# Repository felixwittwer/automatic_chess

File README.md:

# automatic_chess

## grbl firmware v1.1 for movement

[https://github.com/gnea/grbl](https://github.com/gnea/grbl)

Follow the original guide for installation and compilation: [https://github.com/gnea/grbl/wiki/Compiling-Grbl](https://github.com/gnea/grbl/wiki/Compiling-Grbl)

Instead of the original Repository the cusomt configuration in this repository should be used.

##

[Diagram in PDF form](./circuit_diagrams/Diagram.pdf)

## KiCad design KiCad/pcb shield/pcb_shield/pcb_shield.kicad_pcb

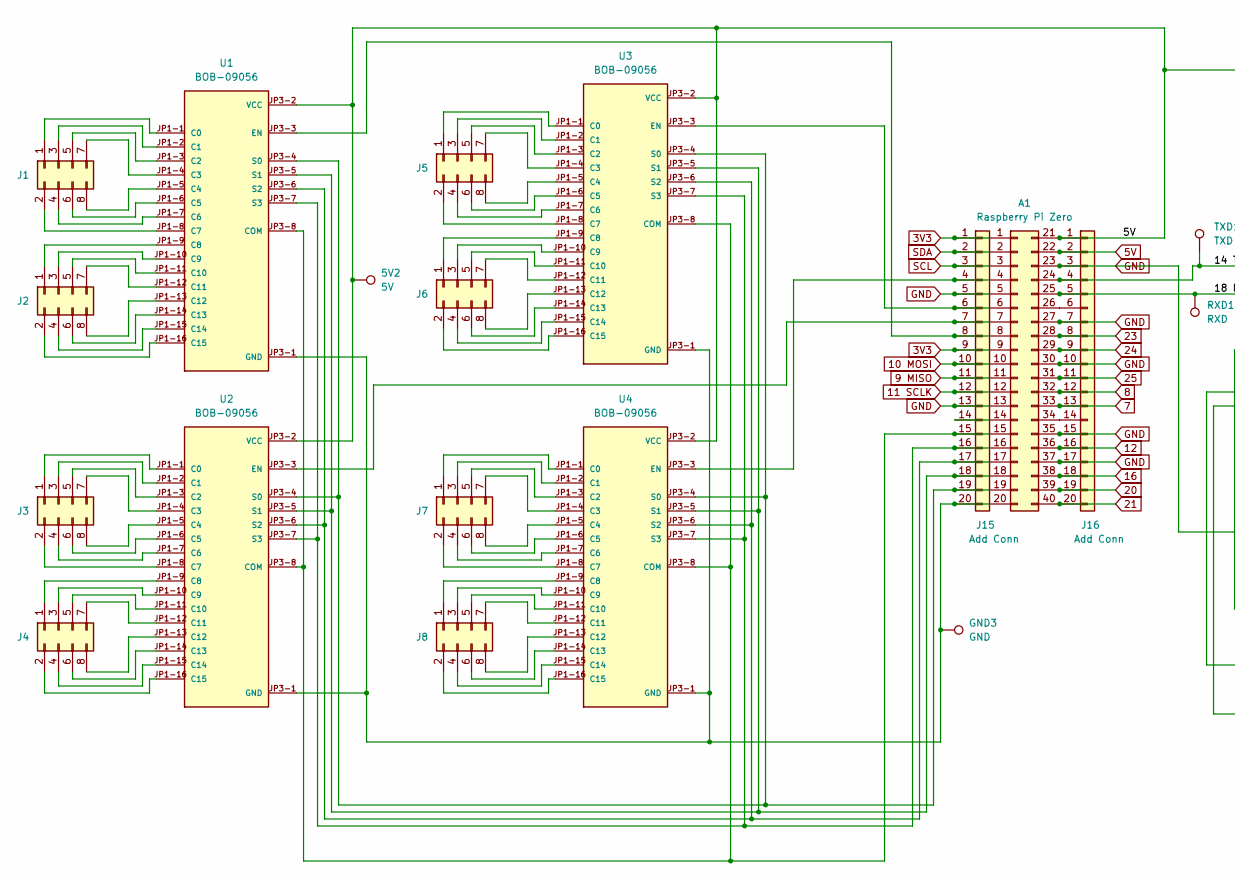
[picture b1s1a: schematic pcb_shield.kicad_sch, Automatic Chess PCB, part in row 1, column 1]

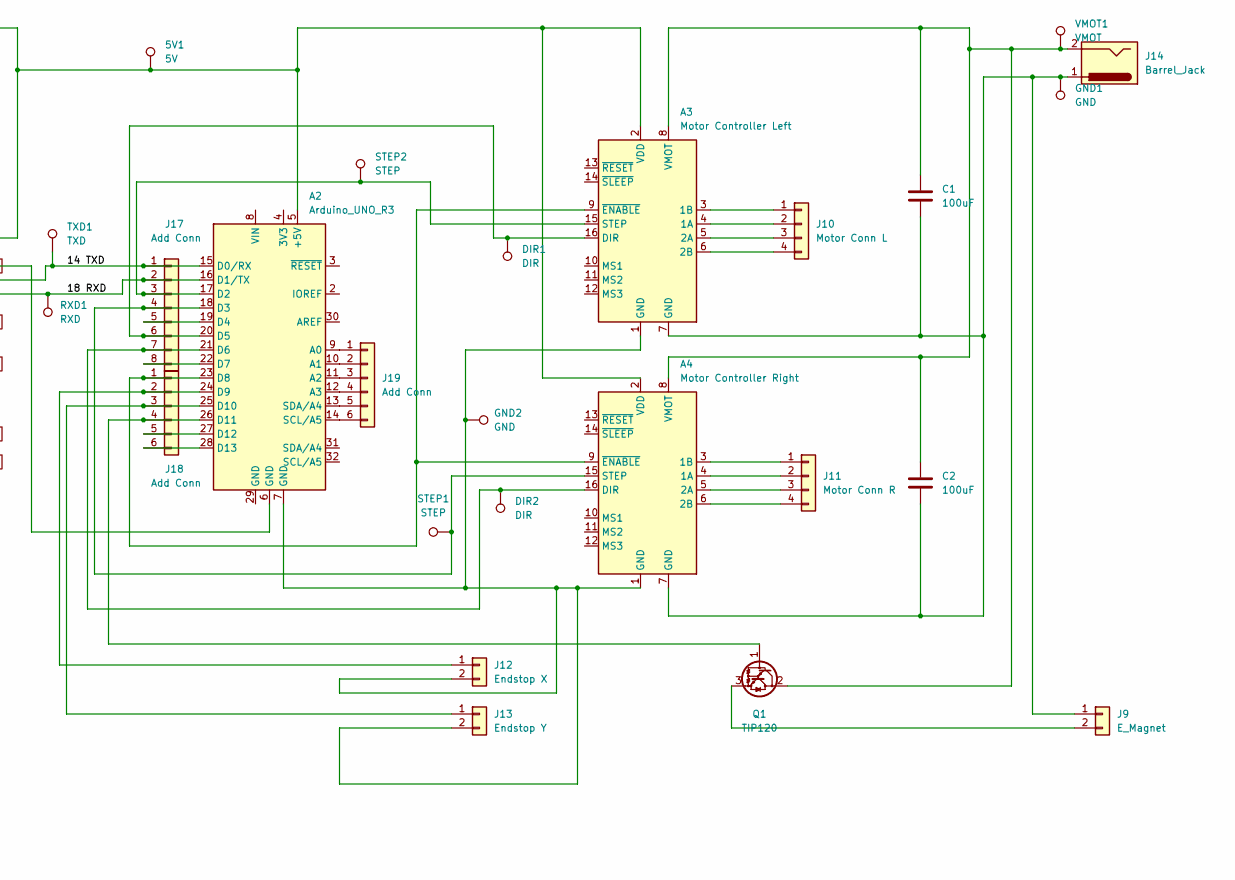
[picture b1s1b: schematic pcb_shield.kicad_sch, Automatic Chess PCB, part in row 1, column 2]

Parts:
5V1, 5V2: 5V; TestPoint_Pad_D2.0mm
A1: Raspberry Pi Zero; PinSocket_2x20_P2.54mm_Vertical
A2: Arduino_UNO_R3
A3: Motor Controller Left; Pololu_Breakout-16_15.2x20.3mm
A4: Motor Controller Right; Pololu_Breakout-16_15.2x20.3mm
C1, C2: 100uF; CP_Radial_D5.0mm_P2.50mm
DIR1, DIR2: DIR; TestPoint_Pad_D2.0mm
GND1, GND2, GND3: GND; TestPoint_Pad_D2.0mm
J1, J2, J3, J4, J5, J6, J7, J8: PinHeader_2x04_P2.54mm_Vertical
J9: E_Magnet; PinHeader_1x02_P2.54mm_Vertical
J10: Motor Conn L; PinHeader_1x04_P2.54mm_Vertical
J11: Motor Conn R; PinHeader_1x04_P2.54mm_Vertical
J12: Endstop X; PinHeader_1x02_P2.54mm_Vertical
J13: Endstop Y; PinHeader_1x02_P2.54mm_Vertical
J14: Barrel_Jack; TerminalBlock_Phoenix_MKDS-1,5-2_1x02_P5.00mm_Horizontal
J15, J16: Add Conn; PinSocket_1x20_P2.54mm_Vertical
J17: Add Conn; PinHeader_1x08_P2.54mm_Vertical
J18, J19: Add Conn; PinHeader_1x06_P2.54mm_Vertical
Q1: TIP120; TO-220-3_Vertical
RXD1: RXD; TestPoint_Pad_D2.0mm
STEP1, STEP2: STEP; TestPoint_Pad_D2.0mm
TXD1: TXD; TestPoint_Pad_D2.0mm
U1, U2, U3, U4: BOB-09056; MODULE_BOB-09056; PARTREV v11
VMOT1: VMOT; TestPoint_Pad_D2.0mm

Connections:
3V3: A1.1, A1.9, J15.1, J15.9
5V: 5V1.1, 5V2.1, A1.21, A1.22, A2.5 (+5V), A3.2 (VDD), A4.2 (VDD), J16.1, J16.2, U1.JP3-2 (VCC), U2.JP3-2 (VCC), U3.JP3-2 (VCC), U4.JP3-2 (VCC)
7: A1.33, J16.13
8: A1.32, J16.12
9 MISO: A1.11, J15.11
10 MOSI: A1.10, J15.10
11 SCLK: A1.12, J15.12
12: A1.36, J16.16
16: A1.38, J16.18
20: A1.39, J16.19
21: A1.40, J16.20
23: A1.28, J16.8
24: A1.29, J16.9
25: A1.31, J16.11
/14 TXD: A1.24, A2.15 (D0/RX), J16.4, J17.1, TXD1.1
/18 RXD: A1.25, A2.16 (D1/TX), J16.5, J17.2, RXD1.1
GND: A1.5, A1.13, A1.23, A1.27, A1.30, A1.35, A1.37, A2.6 (GND), J15.5, J15.13, J16.3, J16.7, J16.10, J16.15, J16.17
unnamed: A1.4, J15.4, U4.JP3-3 (EN)
unnamed: A1.6, J15.6, U3.JP3-3 (EN)
unnamed: A1.7, J15.7, U2.JP3-3 (EN)
unnamed: A1.8, J15.8, U1.JP3-3 (EN)
unnamed: A1.14, J15.14
unnamed: A1.15, J15.15, U1.JP3-8 (COM), U2.JP3-8 (COM), U3.JP3-8 (COM), U4.JP3-8 (COM)
unnamed: A1.16, J15.16, U1.JP3-7 (S3), U2.JP3-7 (S3), U3.JP3-7 (S3), U4.JP3-7 (S3)
unnamed: A1.17, J15.17, U1.JP3-6 (S2), U2.JP3-6 (S2), U3.JP3-6 (S2), U4.JP3-6 (S2)
unnamed: A1.18, J15.18, U1.JP3-5 (S1), U2.JP3-5 (S1), U3.JP3-5 (S1), U4.JP3-5 (S1)
unnamed: A1.19, J15.19, U1.JP3-4 (S0), U2.JP3-4 (S0), U3.JP3-4 (S0), U4.JP3-4 (S0)
unnamed: A1.20, GND3.1, J15.20, U1.JP3-1 (GND), U2.JP3-1 (GND), U3.JP3-1 (GND), U4.JP3-1 (GND)
unnamed: A1.26, J16.6
unnamed: A1.34, J16.14
unnamed: A2.7 (GND), A3.1 (GND), A4.1 (GND), GND2.1, J12.2, J13.2
unnamed: A2.9 (A0), J19.1
unnamed: A2.10 (A1), J19.2
unnamed: A2.11 (A2), J19.3
unnamed: A2.12 (A3), J19.4
unnamed: A2.13 (SDA/A4), J19.5
unnamed: A2.14 (SCL/A5), J19.6
unnamed: A2.17 (D2), A3.15 (STEP), J17.3, STEP2.1
unnamed: A2.18 (D3), A4.15 (STEP), J17.4, STEP1.1
unnamed: A2.19 (D4), J17.5
unnamed: A2.20 (D5), A3.16 (DIR), DIR1.1, J17.6
unnamed: A2.21 (D6), A4.16 (DIR), DIR2.1, J17.7
unnamed: A2.22 (D7), J17.8
unnamed: A2.23 (D8), A3.9 (~ENABLE), A4.9 (~ENABLE), J18.1
unnamed: A2.24 (D9), J12.1, J18.2
unnamed: A2.25 (D10), J13.1, J18.3
unnamed: A2.26 (D11), J18.4, Q1.1 (B)
unnamed: A2.27 (D12), J18.5
unnamed: A2.28 (D13), J18.6
unnamed: A3.3 (1B), J10.1
unnamed: A3.4 (1A), J10.2
unnamed: A3.5 (2A), J10.3
unnamed: A3.6 (2B), J10.4
unnamed: A3.7 (GND), A4.7 (GND), C1.2, C2.2, GND1.1, J9.1, J14.1
unnamed: A3.8 (VMOT), A4.8 (VMOT), C1.1, C2.1, J14.2, Q1.2 (C), VMOT1.1
unnamed: A4.3 (1B), J11.1
unnamed: A4.4 (1A), J11.2
unnamed: A4.5 (2A), J11.3
unnamed: A4.6 (2B), J11.4
unnamed: J1.1, U1.JP1-1 (C0)
unnamed: J1.2, U1.JP1-8 (C7)
unnamed: J1.3, U1.JP1-2 (C1)
unnamed: J1.4, U1.JP1-7 (C6)
unnamed: J1.5, U1.JP1-3 (C2)
unnamed: J1.6, U1.JP1-6 (C5)
unnamed: J1.7, U1.JP1-4 (C3)
unnamed: J1.8, U1.JP1-5 (C4)
unnamed: J2.1, U1.JP1-9 (C8)
unnamed: J2.2, U1.JP1-16 (C15)
unnamed: J2.3, U1.JP1-10 (C9)
unnamed: J2.4, U1.JP1-15 (C14)
unnamed: J2.5, U1.JP1-11 (C10)
unnamed: J2.6, U1.JP1-14 (C13)
unnamed: J2.7, U1.JP1-12 (C11)
unnamed: J2.8, U1.JP1-13 (C12)
unnamed: J3.1, U2.JP1-1 (C0)
unnamed: J3.2, U2.JP1-8 (C7)
unnamed: J3.3, U2.JP1-2 (C1)
unnamed: J3.4, U2.JP1-7 (C6)
unnamed: J3.5, U2.JP1-3 (C2)
unnamed: J3.6, U2.JP1-6 (C5)
unnamed: J3.7, U2.JP1-4 (C3)
unnamed: J3.8, U2.JP1-5 (C4)
unnamed: J4.1, U2.JP1-9 (C8)
unnamed: J4.2, U2.JP1-16 (C15)
unnamed: J4.3, U2.JP1-10 (C9)
unnamed: J4.4, U2.JP1-15 (C14)
unnamed: J4.5, U2.JP1-11 (C10)
unnamed: J4.6, U2.JP1-14 (C13)
unnamed: J4.7, U2.JP1-12 (C11)
unnamed: J4.8, U2.JP1-13 (C12)
unnamed: J5.1, U3.JP1-1 (C0)
unnamed: J5.2, U3.JP1-8 (C7)
unnamed: J5.3, U3.JP1-2 (C1)
unnamed: J5.4, U3.JP1-7 (C6)
unnamed: J5.5, U3.JP1-3 (C2)
unnamed: J5.6, U3.JP1-6 (C5)
unnamed: J5.7, U3.JP1-4 (C3)
unnamed: J5.8, U3.JP1-5 (C4)
unnamed: J6.1, U3.JP1-9 (C8)
unnamed: J6.2, U3.JP1-16 (C15)
unnamed: J6.3, U3.JP1-10 (C9)
unnamed: J6.4, U3.JP1-15 (C14)
unnamed: J6.5, U3.JP1-11 (C10)
unnamed: J6.6, U3.JP1-14 (C13)
unnamed: J6.7, U3.JP1-12 (C11)
unnamed: J6.8, U3.JP1-13 (C12)
unnamed: J7.1, U4.JP1-1 (C0)
unnamed: J7.2, U4.JP1-8 (C7)
unnamed: J7.3, U4.JP1-2 (C1)
unnamed: J7.4, U4.JP1-7 (C6)
unnamed: J7.5, U4.JP1-3 (C2)
unnamed: J7.6, U4.JP1-6 (C5)
unnamed: J7.7, U4.JP1-4 (C3)
unnamed: J7.8, U4.JP1-5 (C4)
unnamed: J8.1, U4.JP1-9 (C8)
unnamed: J8.2, U4.JP1-16 (C15)
unnamed: J8.3, U4.JP1-10 (C9)
unnamed: J8.4, U4.JP1-15 (C14)
unnamed: J8.5, U4.JP1-11 (C10)
unnamed: J8.6, U4.JP1-14 (C13)
unnamed: J8.7, U4.JP1-12 (C11)
unnamed: J8.8, U4.JP1-13 (C12)
unnamed: J9.2, Q1.3 (E)
SCL: A1.3, J15.3
SDA: A1.2, J15.2

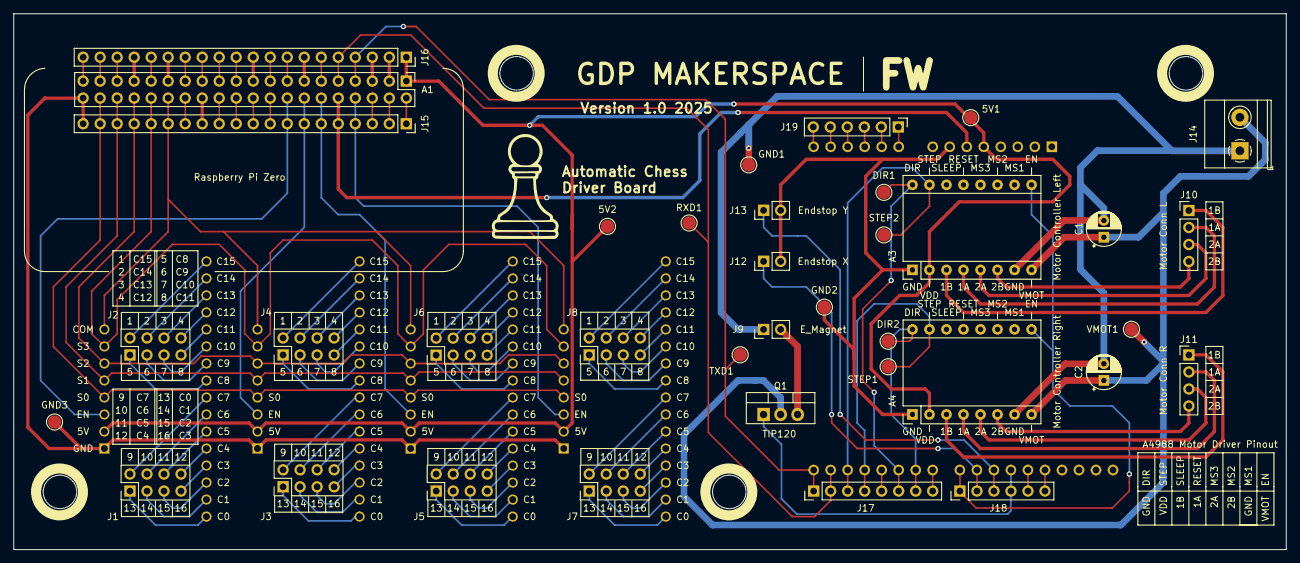
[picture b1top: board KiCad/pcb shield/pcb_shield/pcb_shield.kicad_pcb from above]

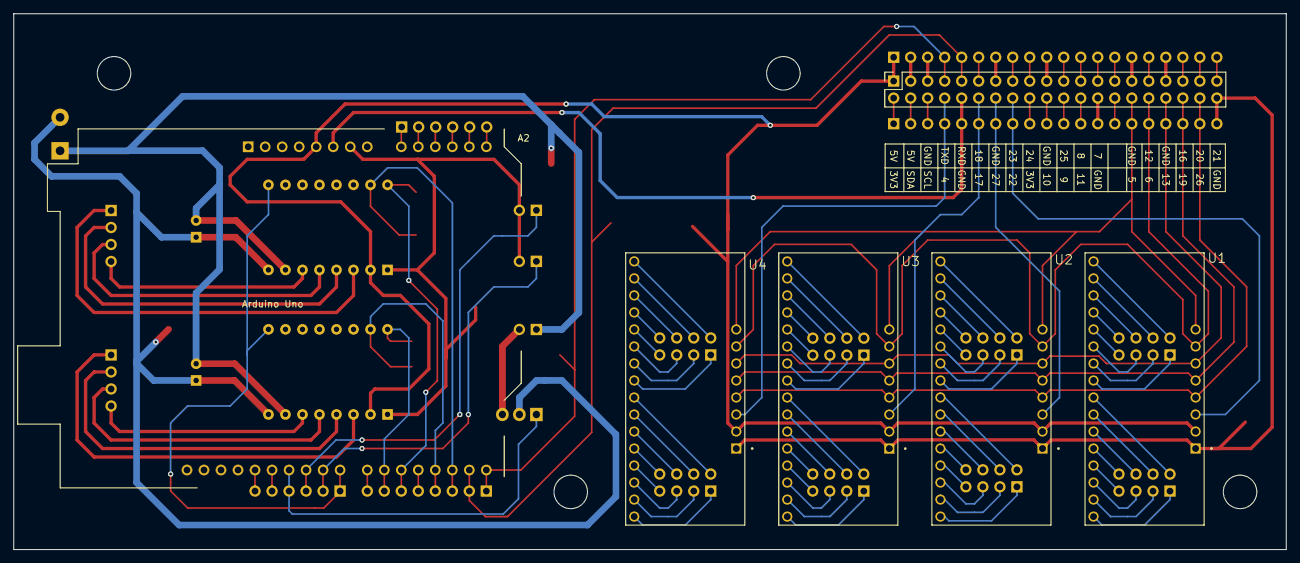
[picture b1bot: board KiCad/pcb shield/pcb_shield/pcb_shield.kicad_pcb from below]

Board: 2 copper layers, 190.0 x 80.0 mm, 42 parts (6 on the bottom side), 126 nets.

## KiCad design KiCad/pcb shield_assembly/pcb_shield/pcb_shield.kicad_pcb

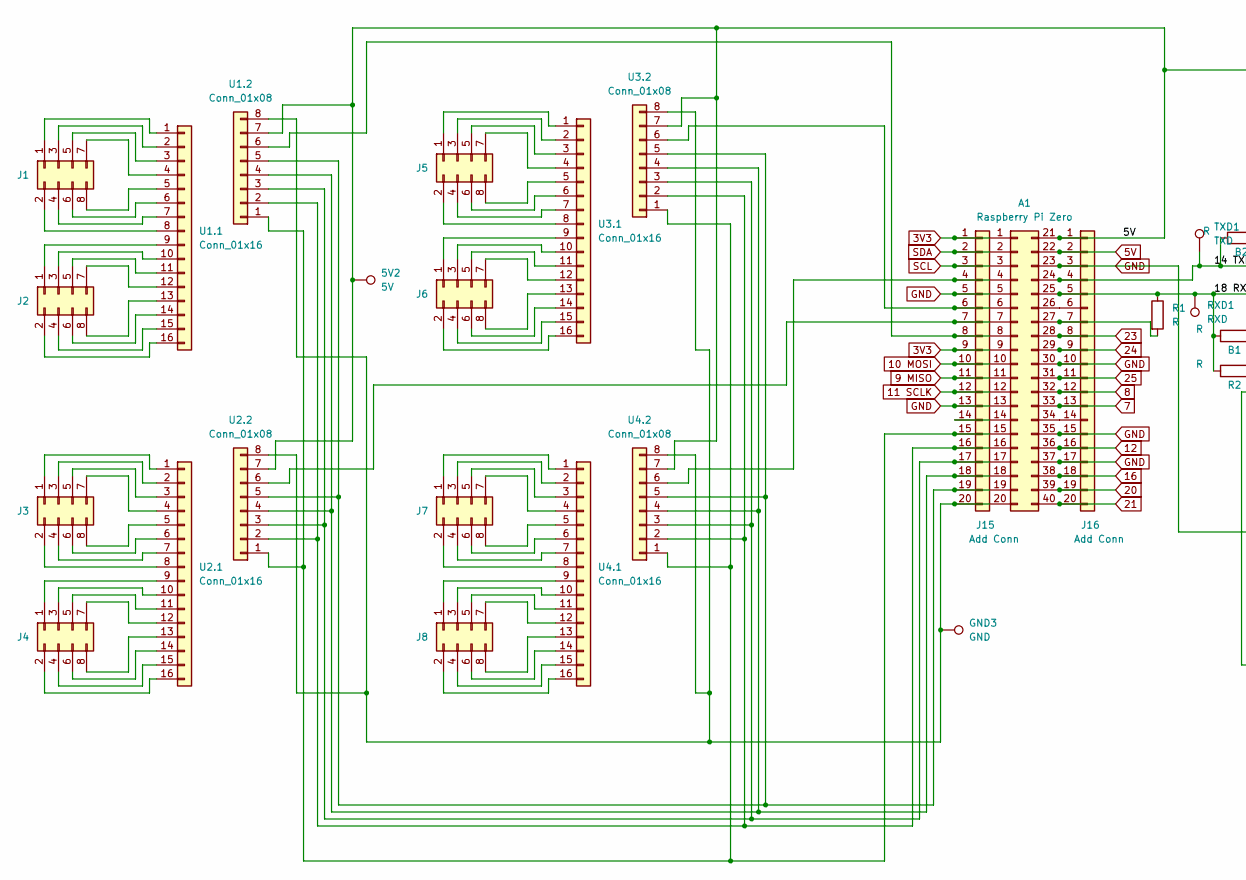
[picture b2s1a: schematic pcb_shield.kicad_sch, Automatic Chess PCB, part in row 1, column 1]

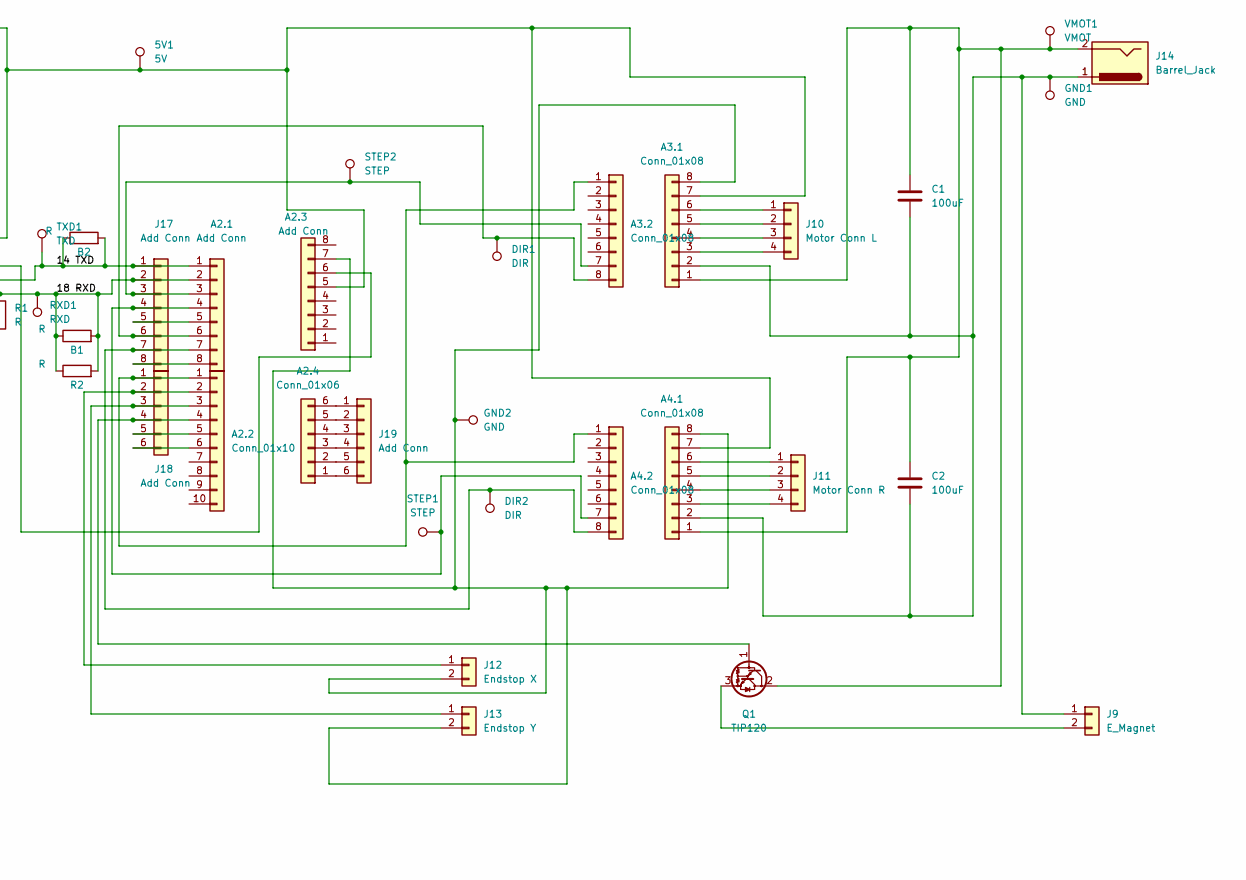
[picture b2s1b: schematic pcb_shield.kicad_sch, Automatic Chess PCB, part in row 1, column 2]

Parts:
5V1, 5V2: 5V; TestPoint_Pad_D2.0mm
A1: Raspberry Pi Zero; PinSocket_2x20_P2.54mm_Vertical
A2.1, A2.3: Add Conn; PinHeader_1x08_P2.54mm_Vertical
A2.2: Conn_01x10; PinHeader_1x10_P2.54mm_Vertical
A2.4: Conn_01x06; PinHeader_1x06_P2.54mm_Vertical
A3.1, A3.2, A4.1, A4.2: Conn_01x08; PinSocket_1x08_P2.54mm_Vertical
B1, B2: R; R_1206_3216Metric_Pad1.30x1.75mm_HandSolder
C1, C2: 100uF; CP_Radial_D5.0mm_P2.50mm
DIR1, DIR2: DIR; TestPoint_Pad_D2.0mm
GND1, GND2, GND3: GND; TestPoint_Pad_D2.0mm
J1, J2, J3, J4, J5, J6, J7, J8: PinHeader_2x04_P2.54mm_Vertical
J9: E_Magnet; PinHeader_1x02_P2.54mm_Vertical
J10: Motor Conn L; PinHeader_1x04_P2.54mm_Vertical
J11: Motor Conn R; PinHeader_1x04_P2.54mm_Vertical
J12: Endstop X; PinHeader_1x02_P2.54mm_Vertical
J13: Endstop Y; PinHeader_1x02_P2.54mm_Vertical
J14: Barrel_Jack; TerminalBlock_Phoenix_MKDS-1,5-2_1x02_P5.00mm_Horizontal
J15, J16: Add Conn; PinSocket_1x20_P2.54mm_Vertical
J17: Add Conn; PinHeader_1x08_P2.54mm_Vertical
J18, J19: Add Conn; PinHeader_1x06_P2.54mm_Vertical
Q1: TIP120; TO-220-3_Vertical
R1, R2: R; R_Axial_DIN0309_L9.0mm_D3.2mm_P12.70mm_Horizontal
RXD1: RXD; TestPoint_Pad_D2.0mm
STEP1, STEP2: STEP; TestPoint_Pad_D2.0mm
TXD1: TXD; TestPoint_Pad_D2.0mm
U1.1, U2.1, U3.1, U4.1: Conn_01x16; PinSocket_1x16_P2.54mm_Vertical
U1.2, U2.2, U3.2, U4.2: Conn_01x08; PinSocket_1x08_P2.54mm_Vertical
VMOT1: VMOT; TestPoint_Pad_D2.0mm

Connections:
3V3: A1.1, A1.9, J15.1, J15.9
5V: 5V1.1, 5V2.1, A1.21, A1.22, A2.3.5, A3.1.7, A4.1.7, J16.1, J16.2, U1.2.7, U2.2.7, U3.2.7, U4.2.7
7: A1.33, J16.13
8: A1.32, J16.12
9 MISO: A1.11, J15.11
10 MOSI: A1.10, J15.10
11 SCLK: A1.12, J15.12
12: A1.36, J16.16
16: A1.38, J16.18
20: A1.39, J16.19
21: A1.40, J16.20
23: A1.28, J16.8
24: A1.29, J16.9
25: A1.31, J16.11
/14 TXD: A1.24, A2.1.1, B2.1, B2.2, J16.4, J17.1, TXD1.1
/18 RXD: A1.25, A2.1.2, B1.1, B1.2, J16.5, J17.2, R1.1, R2.1, R2.2, RXD1.1
GND: A1.5, A1.13, A1.23, A1.30, A1.35, A1.37, A2.3.6, J15.5, J15.13, J16.3, J16.10, J16.15, J16.17
unnamed: A1.4, J15.4, U4.2.6
unnamed: A1.6, J15.6, U3.2.6
unnamed: A1.7, J15.7, U2.2.6
unnamed: A1.14, J15.14
unnamed: A1.15, J15.15, U1.2.1, U2.2.1, U3.2.1, U4.2.1
unnamed: A1.16, J15.16, U1.2.2, U2.2.2, U3.2.2, U4.2.2
unnamed: A1.17, J15.17, U1.2.3, U2.2.3, U3.2.3, U4.2.3
unnamed: A1.18, J15.18, U1.2.4, U2.2.4, U3.2.4, U4.2.4
unnamed: A1.19, J15.19, U1.2.5, U2.2.5, U3.2.5, U4.2.5
unnamed: A1.20, GND3.1, J15.20, U1.2.8, U2.2.8, U3.2.8, U4.2.8
unnamed: A1.26, J16.6
unnamed: A1.27, J16.7, R1.2
unnamed: A1.34, J16.14
unnamed: A2.3.7, A3.1.8, A4.1.8, GND2.1, J12.2, J13.2
unnamed: A3.1.1, A4.1.1, C1.1, C2.1, J14.2, Q1.2 (C), VMOT1.1
unnamed: A3.1.2, A4.1.2, C1.2, C2.2, GND1.1, J9.1, J14.1
unnamed: A3.1.3, J10.4
unnamed: A3.1.4, J10.3
unnamed: A3.1.5, J10.2
unnamed: A3.1.6, J10.1
unnamed: A2.2.1, A3.2.1, A4.2.1, J18.1
unnamed: A2.1.3, A3.2.7, J17.3, STEP2.1
unnamed: A2.1.6, A3.2.8, DIR1.1, J17.6
unnamed: A2.1.4, A4.2.7, J17.4, STEP1.1
unnamed: A2.1.7, A4.2.8, DIR2.1, J17.7
unnamed: J1.1, U1.1.1
unnamed: J1.2, U1.1.8
unnamed: J1.3, U1.1.2
unnamed: J1.4, U1.1.7
unnamed: J1.5, U1.1.3
unnamed: J1.6, U1.1.6
unnamed: J1.7, U1.1.4
unnamed: J1.8, U1.1.5
unnamed: J2.1, U1.1.9
unnamed: J2.2, U1.1.16
unnamed: J2.3, U1.1.10
unnamed: J2.4, U1.1.15
unnamed: J2.5, U1.1.11
unnamed: J2.6, U1.1.14
unnamed: J2.7, U1.1.12
unnamed: J2.8, U1.1.13
unnamed: J3.1, U2.1.1
unnamed: J3.2, U2.1.8
unnamed: J3.3, U2.1.2
unnamed: J3.4, U2.1.7
unnamed: J3.5, U2.1.3
unnamed: J3.6, U2.1.6
unnamed: J3.7, U2.1.4
unnamed: J3.8, U2.1.5
unnamed: J4.1, U2.1.9
unnamed: J4.2, U2.1.16
unnamed: J4.3, U2.1.10
unnamed: J4.4, U2.1.15
unnamed: J4.5, U2.1.11
unnamed: J4.6, U2.1.14
unnamed: J4.7, U2.1.12
unnamed: J4.8, U2.1.13
unnamed: J5.1, U3.1.1
unnamed: J5.2, U3.1.8
unnamed: J5.3, U3.1.2
unnamed: J5.4, U3.1.7
unnamed: J5.5, U3.1.3
unnamed: J5.6, U3.1.6
unnamed: J5.7, U3.1.4
unnamed: J5.8, U3.1.5
unnamed: J6.1, U3.1.9
unnamed: J6.2, U3.1.16
unnamed: J6.3, U3.1.10
unnamed: J6.4, U3.1.15
unnamed: J6.5, U3.1.11
unnamed: J6.6, U3.1.14
unnamed: J6.7, U3.1.12
unnamed: J6.8, U3.1.13
unnamed: J7.1, U4.1.1
unnamed: J7.2, U4.1.8
unnamed: J7.3, U4.1.2
unnamed: J7.4, U4.1.7
unnamed: J7.5, U4.1.3
unnamed: J7.6, U4.1.6
unnamed: J7.7, U4.1.4
unnamed: J7.8, U4.1.5
unnamed: J8.1, U4.1.9
unnamed: J8.2, U4.1.16
unnamed: J8.3, U4.1.10
unnamed: J8.4, U4.1.15
unnamed: J8.5, U4.1.11
unnamed: J8.6, U4.1.14
unnamed: J8.7, U4.1.12
unnamed: J8.8, U4.1.13
unnamed: J9.2, Q1.3 (E)
unnamed: A4.1.6, J11.1
unnamed: A4.1.5, J11.2
unnamed: A4.1.4, J11.3
unnamed: A4.1.3, J11.4
unnamed: A2.2.2, J12.1, J18.2
unnamed: A2.2.3, J13.1, J18.3
unnamed: A2.1.5, J17.5
unnamed: A2.1.8, J17.8
unnamed: A2.2.4, J18.4, Q1.1 (B)
unnamed: A2.2.5, J18.5
unnamed: A2.2.6, J18.6
unnamed: A2.4.6, J19.1
unnamed: A2.4.5, J19.2
unnamed: A2.4.4, J19.3
unnamed: A2.4.3, J19.4
unnamed: A2.4.2, J19.5
unnamed: A2.4.1, J19.6
unnamed: A1.8, J15.8, U1.2.6
SCL: A1.3, J15.3
SDA: A1.2, J15.2

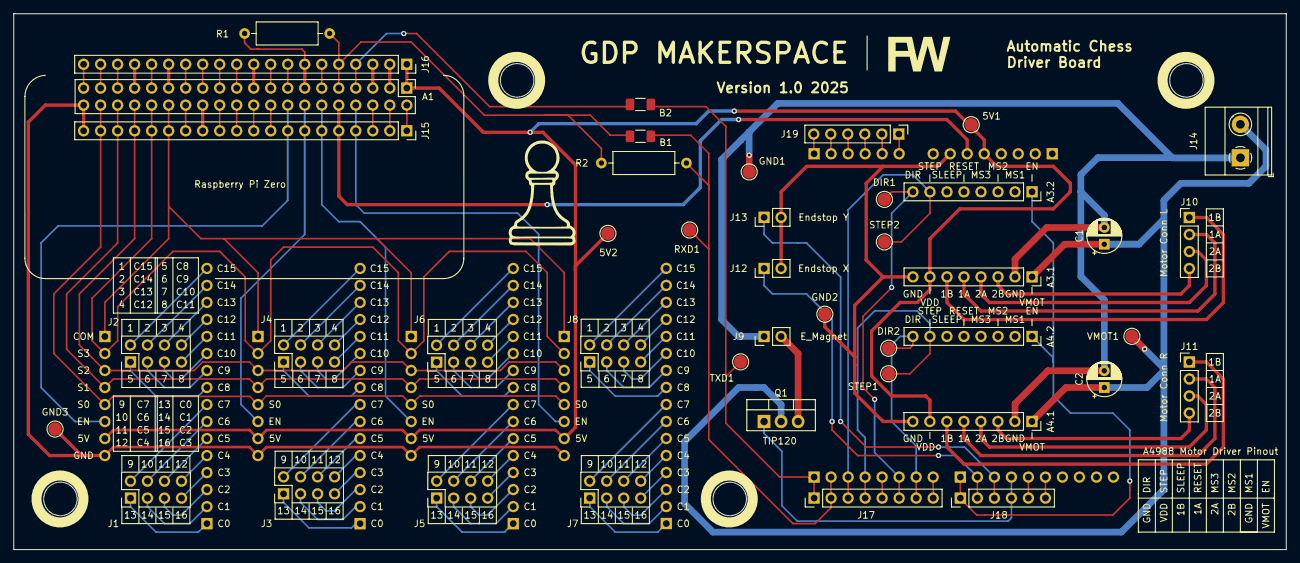
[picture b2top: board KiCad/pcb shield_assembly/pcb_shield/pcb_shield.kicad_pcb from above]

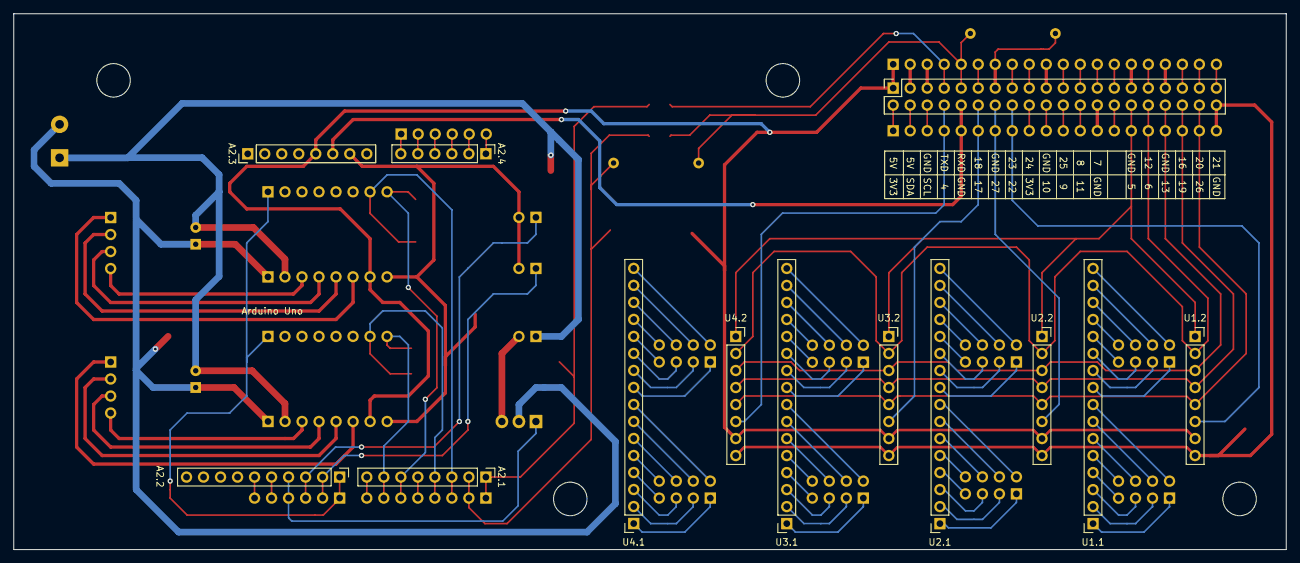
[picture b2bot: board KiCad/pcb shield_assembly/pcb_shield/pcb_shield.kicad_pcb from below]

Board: 2 copper layers, 190.0 x 80.0 mm, 55 parts (13 on the bottom side), 127 nets.

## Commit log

2024-09-18 create file for testing a single stepper motor
2024-09-21 add codefiles from instructables
2024-09-24 add dual motor control
    with static values and direction
2024-10-01 build terminal like control of motors via serial monitor
2024-10-02 add superposition motor control
2024-10-16 add KiCad files
2024-10-16 finish motor diagram
2024-10-16 add circuit diagrams to README
2024-11-26 add script for controlling the motors individually
2024-12-01 add motortester script
    Add script to test and understand functionality of a singe motor by manually inputing the parameters over serial.
2024-12-15 reorganize files
2024-12-15 add datasheet and other documentation
2024-12-15 add another more detailed datasheet
2024-12-21 add customized 3d files
2024-12-22 modifying support pully A and B files add stl and sliced files for 3D printing
2024-12-23 start adding new main controler script
2024-12-23 add formulas for movement
2024-12-24 add magnet functionality
2024-12-25 add custom grbl firmware files
2024-12-25 update README with grbl installation info
2024-12-28 start adding serial interafce with python
2024-12-28 add settings preset for our coreXY machine
2025-01-01 enable and setup homing and add starting routine with G-Code
2025-01-01 add magnet commands
2025-01-05 reorder files and further try to interface grbl wiht python
2025-01-05 extend circuit diagram
2025-02-05 add multiplexer documentation
2025-02-05 add multiplexer code
2025-04-08 KiCad stuff for PCB
2025-04-08 add main parts
2025-04-08 start with pcb
2025-04-08 adding multiplexers
2025-04-08 almost finished pcb
2025-04-09 add aditional headers
2025-04-12 working on PCB and creating manufacturing files
2025-04-13 add files for pcb assembly
2025-04-13 make files for hackclub pcb grant
2025-05-27 adding 3d files for organisation parts
2025-05-29 adding mount pieces for plexiglas sheet
